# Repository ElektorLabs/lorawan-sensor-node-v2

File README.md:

# LoRa-Sensor-Node-v2

A comprehensive ESP32-S3 based sensor node that validates GPS positioning, LoRaWAN connectivity, SD card logging, battery charging, and deep-sleep power management without requiring the Arduino IDE.

## 🚀 Features

- **Multi-Peripheral Validation**: Powers and tests GPS, LoRa modem, SD logger, and battery charger
- **Smart Power Management**: Configurable deep-sleep cycles with peripheral power control
- **LoRaWAN Integration**: OTAA join with synthetic telemetry transmission
- **GPS Cold Start Handling**: Waits for valid GPS fix before LoRaWAN operations
- **Battery Management**: BQ25186 charger monitoring and configuration
- **Comprehensive Logging**: Tagged UART output and SD card data logging
- **Status Indicators**: LED patterns for system health monitoring

## 🔧 Hardware Components

### Core Platform
- **MCU**: ESP32-S3 Development Module
- **GPS Module**: Ebyte EWM108-GN05 (Allystar-compatible GNSS receiver)
- **LoRa Module**: Ebyte LoRaWAN module with AT command interface
- **Battery Charger**: BQ25186 Li-Ion battery management IC
- **Storage**: MicroSD card for data logging

### Pin Configuration

| Component | Pin | Function |
|-----------|-----|----------|
| **Power Control** |
| I2C Enable | GPIO 38 | I2C bus power control |
| LoRa Enable | GPIO 6 | LoRa module power |
| GPS Enable | GPIO 7 | GPS module power |
| **Status LEDs** |
| Red LED | GPIO 48 | Error/fault indication |
| Green LED | GPIO 47 | System status |
| **I2C Bus** |
| SDA | GPIO 10 | I2C data line |
| SCL | GPIO 9 | I2C clock line |
| **SD Card (SPI)** |
| MOSI | GPIO 11 | SPI data out |
| SCK | GPIO 12 | SPI clock |
| MISO | GPIO 13 | SPI data in |
| CS | GPIO 8 | Chip select |
| **LoRa UART** |
| RX | GPIO 4 | LoRa module RX |
| TX | GPIO 5 | LoRa module TX |
| **GPS UART** |
| RX | GPIO 21 | GPS module RX |
| TX | GPIO 14 | GPS module TX |

## ⚙️ Configuration

All configuration is centralized in `config.h` using `constexpr` constants:

### Timing Parameters
```cpp
constexpr unsigned long kGpsColdStartMs = 60000;        // GPS cold start window
constexpr unsigned long kGpsLockTimeoutMs = 180000;     // GPS fix timeout
constexpr unsigned long kSensorAcquisitionMs = 15000;   // Sensor reading time
constexpr uint64_t kDeepSleepIntervalUs = 60ULL * 1000000ULL; // Sleep interval
constexpr unsigned long kLoraJoinRetryMs = 15000;       // LoRa join retry
```

### Power Management
```cpp
constexpr bool kEnableDeepSleep = true;     // Enable ESP32 deep sleep
constexpr bool kEnableStatusLeds = true;    // Enable LED indicators
constexpr float kChargeTargetCurrentMa = 520.0f;   // Battery charge current (5-1000 mA)
constexpr float kInputCurrentLimitMa = 665.0f;     // Input current limit (50-665 mA)
```

### LoRaWAN Credentials
```cpp
constexpr LoraCredentials kLoraCredentials{
    "xxxxxxxxxxxxxxxx",                    // Device EUI
    "0000000000000000",                    // Application EUI
    "xxxxxxxxxxxxxxxxxxxxxxxxxxxxxx",   // Application Key
};
```

### GPS Power Configuration
```cpp
constexpr AllystarGpsPowerConfig kGpsPowerConfig{
    true,    // Enable GPS sleep/wake commands
    90000,   // Sleep duration (90 seconds)
    0x01,    // Sleep action (deep sleep)
    0x11,    // Wake mode (start command)
};
```

## 🔄 Operation Flow

1. **System Wake**: ESP32 wakes from deep sleep, powers peripheral rails
2. **GPS Cold Start**: Waits for GPS module to acquire satellite fix
3. **LoRaWAN Join**: Performs OTAA join once GPS is ready (or timeout expires)
4. **Data Collection**: Gathers GPS coordinates and battery telemetry
5. **Transmission**: Sends telemetry via LoRaWAN uplink
6. **Logging**: Records data to SD card with timestamps
7. **Sleep Preparation**: Powers down GPS with Allystar sleep commands
8. **Deep Sleep**: ESP32 enters deep sleep for configured interval

## 📊 Serial Output

The firmware provides tagged serial output at 115200 baud:

```
[Pwr ] Wake reason: Timer
[GPS ] Powering GPS module...
[LoRa] Powering LoRa module...
[GPS ] NMEA: $GNGGA,123456.00,4012.34567,N,07412.34567,W,1,08,1.2,45.6,M,33.2,M,,*5A
[LoRa] AT+JOIN
[LoRa] Event: join confirmed
[LoRa] Sending telemetry: 4012.34567,-07412.34567,45.6,4.12,85
[Chg ] Battery: 4.12V, Charge: 85%, Temp: 25°C
[Pwr ] Entering deep sleep for 60 seconds
```

## 📁 File Structure

```
LoRa-SenseNode-v2/
├── LoRa-SenseNode-v2.ino    # Main firmware file
├── config.h                 # Configuration constants
├── Bq25186.h               # Battery charger interface
├── EbyteGpsParser.h        # GPS NMEA parser
├── LoraAtHelpers.h         # LoRaWAN AT command helpers
├── SdCardLogger.h          # SD card logging utilities
├── TaggedStream.h          # Serial output tagging
├── ProcessFlow.md          # Detailed process documentation
├── FirmwareOverview.md     # Architecture overview
└── docs/                   # Additional documentation
```

## 🔍 Troubleshooting

### LED Status Indicators
- **2 Red Blinks**: GPS fault or timeout
- **3 Red Blinks**: LoRa communication fault
- **Green Solid**: System operating normally
- **LEDs Off**: Status LEDs disabled in config

### Common Issues
1. **GPS Not Acquiring Fix**: Ensure clear sky view, check antenna connection
2. **LoRa Join Fails**: Verify credentials and gateway availability
3. **SD Card Errors**: Check card formatting (FAT32) and connections
4. **Power Issues**: Verify battery connection and charger configuration

### Debug Mode
Set `kEnableDebugSerial = true` and `kShowRawGps = true` in config.h for verbose output.

## 🛠️ Development

### Adding New Features
- Hardware tests: Create new sketches in `src/tests/<SketchName>/`
- Experiments: Use `src/claude-test/` for exploratory code
- Helper functions: Add to existing headers or create new ones as needed

### Testing Without Deep Sleep
Set `kEnableDeepSleep = false` in config.h to run continuous loops for bench testing.

## 📄 License

This project is licensed under the GNU License - see the [LICENSE](LICENSE) file for details.

## 🤝 Contributing

1. Fork the repository
2. Create a feature branch (`git checkout -b feature/amazing-feature`)
3. Commit your changes (`git commit -m 'Add amazing feature'`)
4. Push to the branch (`git push origin feature/amazing-feature`)
5. Open a Pull Request

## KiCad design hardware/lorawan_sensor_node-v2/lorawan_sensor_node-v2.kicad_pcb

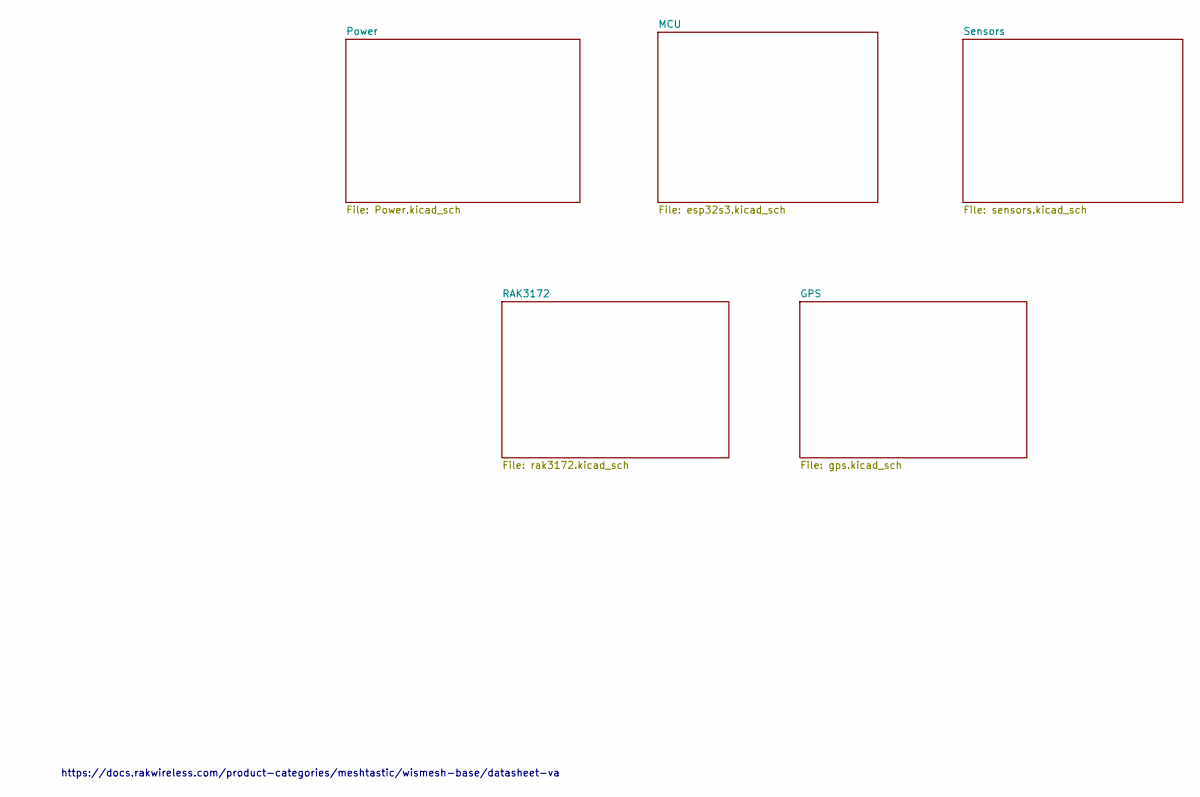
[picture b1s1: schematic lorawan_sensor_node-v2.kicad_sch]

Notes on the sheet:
https://docs.rakwireless.com/product-categories/meshtastic/wismesh-base/datasheet-va

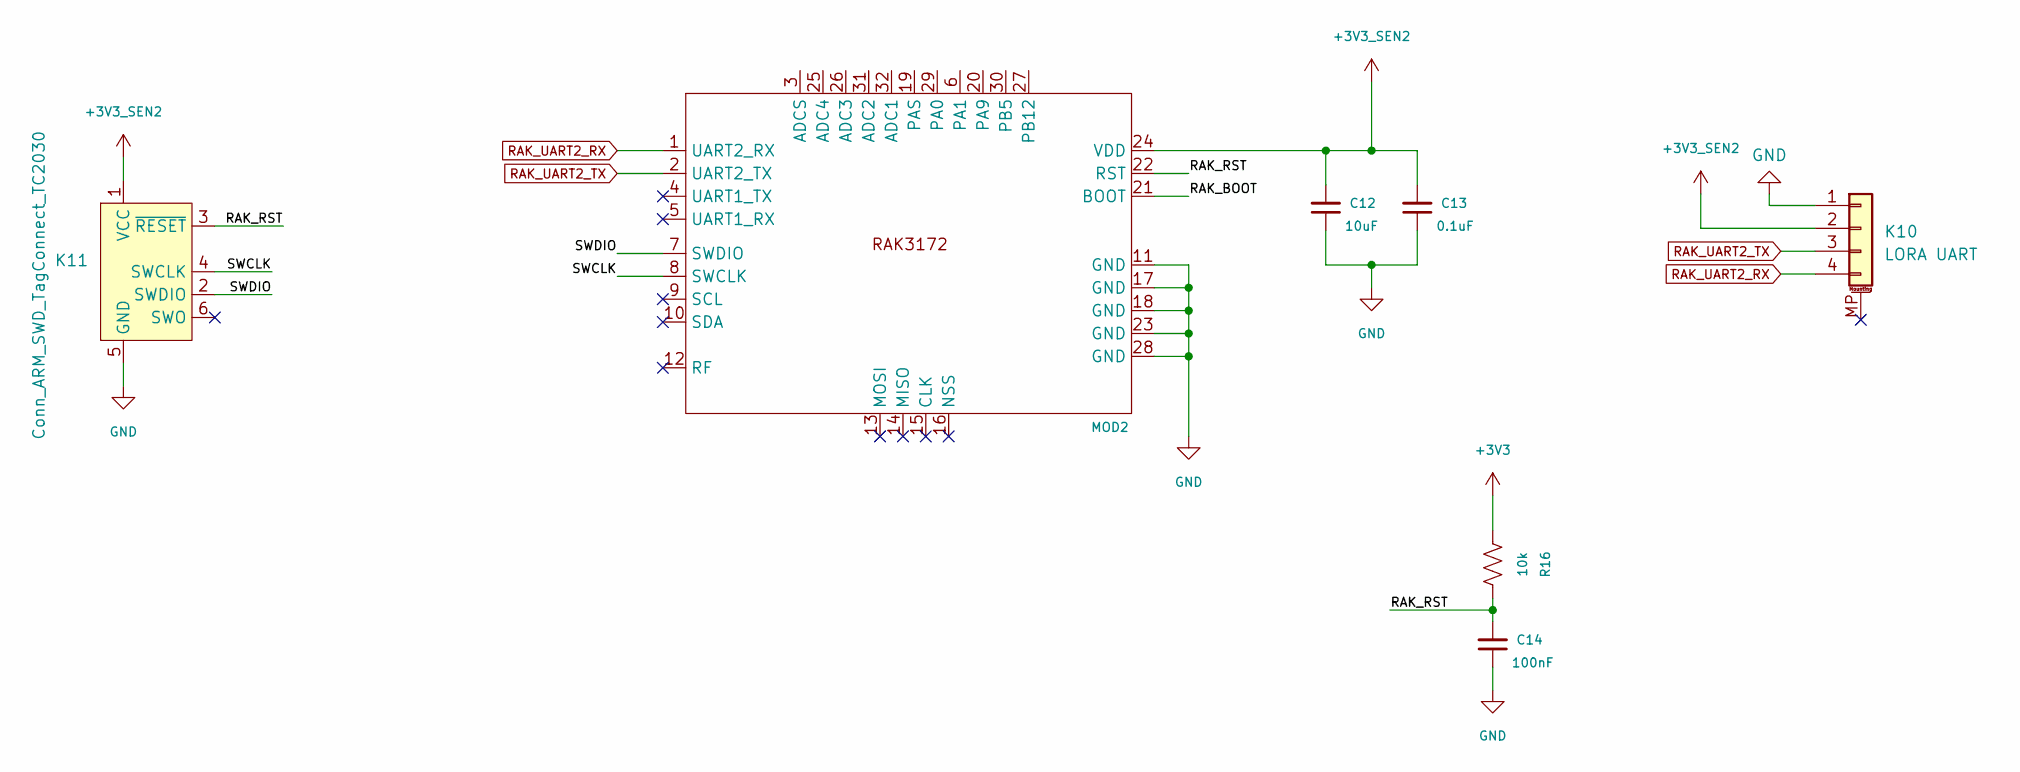
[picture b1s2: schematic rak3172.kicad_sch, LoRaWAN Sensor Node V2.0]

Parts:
C12: 10uF; C_0402_1005Metric_Pad0.74x0.62mm_HandSolder; Mouser Part Number 81-GRM155R60J475ME7D
C13: 0.1uF; C_0402_1005Metric_Pad0.74x0.62mm_HandSolder; Mouser Part Number 81-GRM155R60J475ME7D
C14: 100nF; C_0402_1005Metric_Pad0.74x0.62mm_HandSolder; Mouser Part Number 81-GRM155R60J475ME7D
K10: LORA UART; JST_PH_S4B-PH-SM4-TB_1x04-1MP_P2.00mm_Horizontal; Manufacturer_Part_Number Connector_JST:JST_PH_S4B-PH-SM4-TB_1x04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
K11: Conn_ARM_SWD_TagConnect_TC2030; Tag-Connect_TC2030-IDC-NL_2x03_P1.27mm_Vertical
MOD2: RAK3172; Manufacturer_Part_Number RAK3172
R16: 10k; R_0603_1608Metric; Manufacturer_Part_Number RCS060310K0FKEA; Mouser Part Number 71-RCS060310K0FKEA

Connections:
+3V3: R16.2; also elsewhere on the board
+3V3_SEN2: C12.2, C13.2, K10.2, K11.1 (VCC), MOD2.24 (VDD); also elsewhere on the board
/RAK3172/RAK_BOOT: MOD2.21 (BOOT)
/RAK3172/RAK_RST: C14.2, K11.3 (~RESET), MOD2.22 (RST), R16.1
/RAK3172/SWCLK: K11.4 (SWCLK), MOD2.8 (SWCLK)
/RAK3172/SWDIO: K11.2 (SWDIO), MOD2.7 (SWDIO)
GND: C12.1, C13.1, C14.1, K10.1, K11.5 (GND), MOD2.11 (GND), MOD2.17 (GND), MOD2.18 (GND), MOD2.23 (GND), MOD2.28 (GND); also elsewhere on the board
RAK_UART2_RX: K10.4, MOD2.1 (UART2_RX); also elsewhere on the board
RAK_UART2_TX: K10.3, MOD2.2 (UART2_TX); also elsewhere on the board

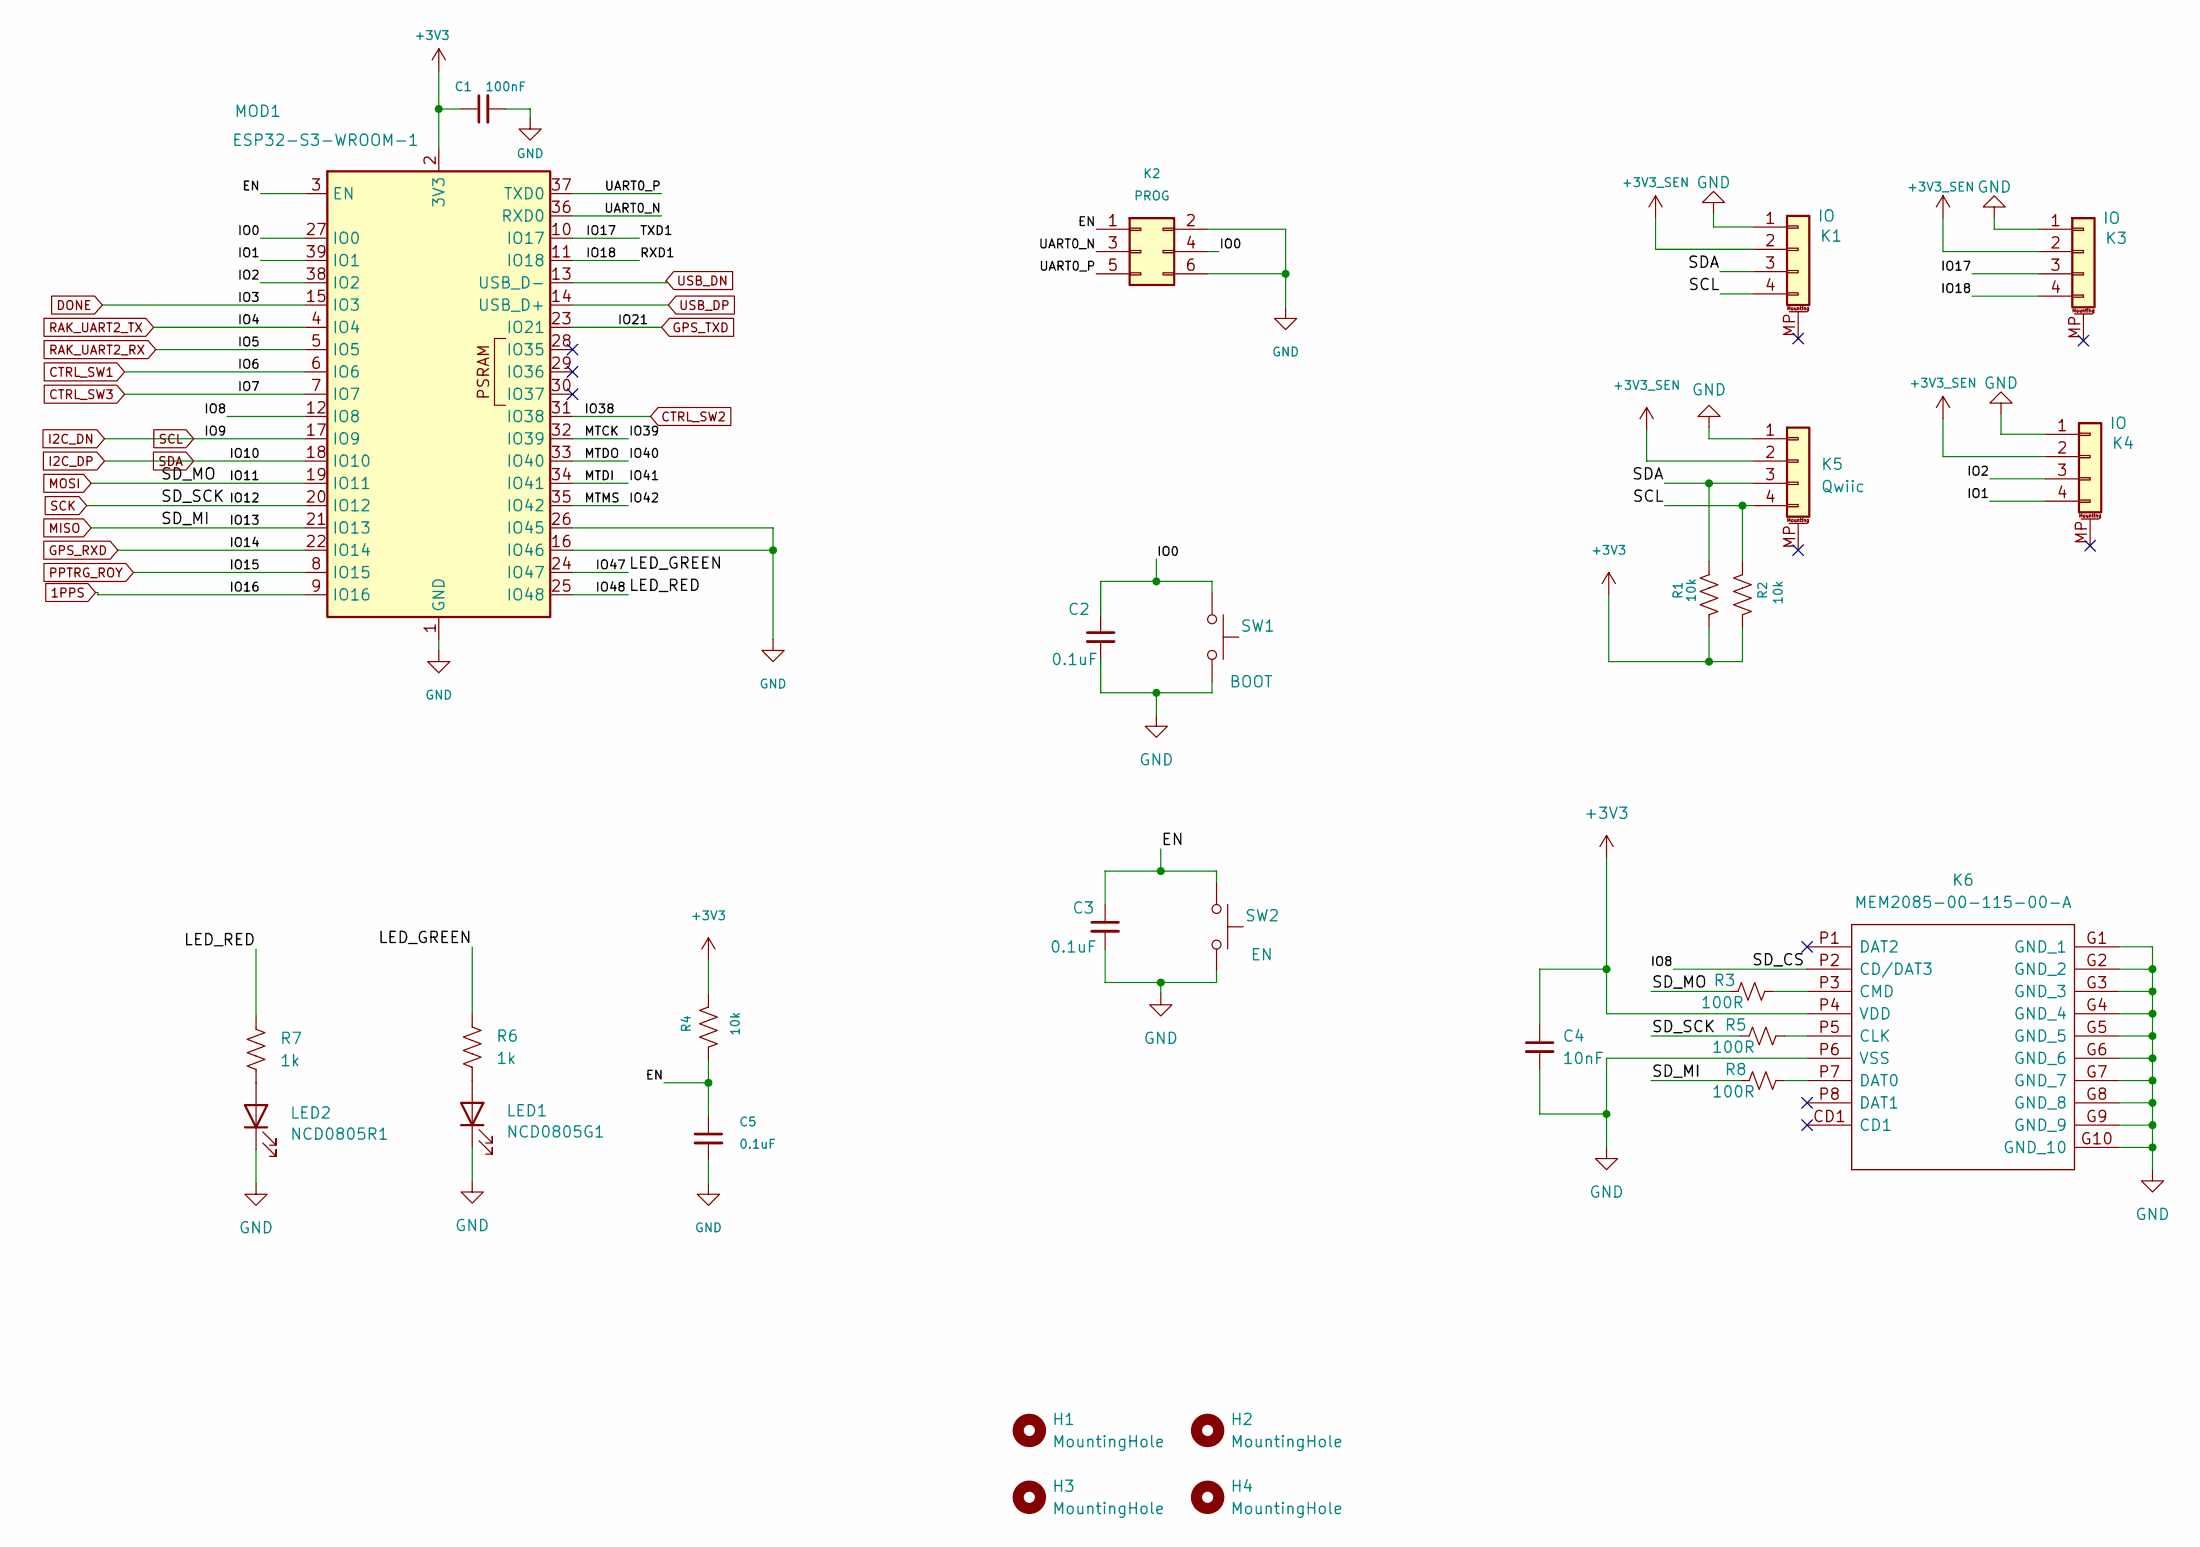
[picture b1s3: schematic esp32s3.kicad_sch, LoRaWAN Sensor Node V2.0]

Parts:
C1: 100nF; C_0603_1608Metric; Manufacturer_Part_Number C1608X7R1H104K080AA; Mouser Part Number 810-C1608X7R1H104K
C2, C3: 0.1uF; C_0805_2012Metric_Pad1.18x1.45mm_HandSolder; Manufacturer_Part_Number C0805C104M5RACTU; Mouser Part Number 80-C0805C104M5R
C4: 10nF; C_0402_1005Metric_Pad0.74x0.62mm_HandSolder; Manufacturer_Part_Number C0402C103K5RAC7411; Mouser Part Number 80-C0402C103K5R7411
C5: 0.1uF; C_0603_1608Metric; Manufacturer_Part_Number C1608X7R1H104K080AA; Mouser Part Number 810-C1608X7R1H104K
H1, H2, H3, H4: MountingHole; MountingHole_3.2mm_M3
K1, K3, K4: IO; JST_PH_S4B-PH-SM4-TB_1x04-1MP_P2.00mm_Horizontal; Manufacturer_Part_Number JST_PH_S4B-PH-SM4-TB_1x04-1MP_P2.00mm_H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
K2: PROG; PinHeader_2x03_P2.54mm_Vertical; Manufacturer_Part_Number PinHeader_2x03_P2.54mm_Vertical
K5: Qwiic; JST_SH_SM04B-SRSS-TB_1x04-1MP_P1.00mm_Horizontal; Manufacturer_Part_Number JST_SH_SM04B-SRSS-TB_1x04-1MP_P1.00mm_H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
K6: MEM2085-00-115-00-A; MEM20850011500A; Mouser Part Number 640-MEM20850011500A
LED1: NCD0805G1; LED_0805_2012Metric_Pad1.15x1.40mm_HandSolder; Manufacturer_Part_Number NCD0805G1
LED2: NCD0805R1; LED_0805_2012Metric_Pad1.15x1.40mm_HandSolder; Manufacturer_Part_Number NCD0805R1
MOD1: ESP32-S3-WROOM-1; Manufacturer_Part_Number ESP32-S3-WROOM-1
R1, R2, R4: 10k; R_0603_1608Metric; Manufacturer_Part_Number RCS060310K0FKEA; Mouser Part Number 71-RCS060310K0JNEA
R3, R5, R8: 100R; R_0603_1608Metric; Manufacturer_Part_Number MCT0603PD1000DP500; Mouser Part Number 594-MCT0603PD1000DP5
R6, R7: 1k; R_0805_2012Metric_Pad1.20x1.40mm_HandSolder; Manufacturer_Part_Number CHP0805-FX-1001ELF; Mouser Part Number 652-CHP0805FX1001ELF
SW1: BOOT; SKRKAEE020; Manufacturer_Part_Number SKRKAEE020; Mouser Part Number SKRKAEE020
SW2: EN; SKRKAEE020; Manufacturer_Part_Number SKRKAEE020; Mouser Part Number SKRKAEE020

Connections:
1PPS: MOD1.9 (IO16); also elsewhere on the board
+3V3: C1.1, C4.1, K6.P4 (VDD), MOD1.2 (3V3), R1.1, R2.1, R4.2; also elsewhere on the board
+3V3_SEN: K1.2, K3.2, K4.2, K5.2; also elsewhere on the board
/MCU/EN: C3.1, C5.1, K2.1, MOD1.3 (EN), R4.1, SW2.1
/MCU/IO0: C2.1, K2.4, MOD1.27 (IO0), SW1.1
/MCU/IO1: K4.4, MOD1.39 (IO1)
/MCU/IO2: K4.3, MOD1.38 (IO2)
/MCU/IO8: K6.P2 (CD/DAT3), MOD1.12 (IO8)
/MCU/IO17: K3.3, MOD1.10 (IO17)
/MCU/IO18: K3.4, MOD1.11 (IO18)
/MCU/IO39: MOD1.32 (IO39)
/MCU/IO40: MOD1.33 (IO40)
/MCU/IO41: MOD1.34 (IO41)
/MCU/IO42: MOD1.35 (IO42)
/MCU/IO47: MOD1.24 (IO47), R6.2
/MCU/IO48: MOD1.25 (IO48), R7.2
/MCU/UART0_N: K2.3, MOD1.36 (RXD0)
/MCU/UART0_P: K2.5, MOD1.37 (TXD0)
CTRL_SW1: MOD1.6 (IO6); also elsewhere on the board
CTRL_SW2: MOD1.31 (IO38); also elsewhere on the board
CTRL_SW3: MOD1.7 (IO7); also elsewhere on the board
DONE: MOD1.15 (IO3); also elsewhere on the board
GND: C1.2, C2.2, C3.2, C4.2, C5.2, K1.1, K2.2, K2.6, K3.1, K4.1, K5.1, K6.G1 (GND_1), K6.G2 (GND_2), K6.G3 (GND_3), K6.G4 (GND_4), K6.G5 (GND_5), K6.G6 (GND_6), K6.G7 (GND_7), K6.G8 (GND_8), K6.G9 (GND_9), K6.G10 (GND_10), K6.P6 (VSS), LED1.1 (K), LED2.1 (K), MOD1.1 (GND), MOD1.16 (IO46), MOD1.26 (IO45), MOD1.40 (GND), MOD1.41 (GND), SW1.2, SW2.2; also elsewhere on the board
GPS_RXD: MOD1.22 (IO14); also elsewhere on the board
GPS_TXD: MOD1.23 (IO21); also elsewhere on the board
I2C_DN: K1.4, K5.4, MOD1.17 (IO9), R2.2; also elsewhere on the board
I2C_DP: K1.3, K5.3, MOD1.18 (IO10), R1.2; also elsewhere on the board
MISO: MOD1.21 (IO13), R8.1
MOSI: MOD1.19 (IO11), R3.1
unnamed: K6.P5 (CLK), R5.2
unnamed: K6.P3 (CMD), R3.2
unnamed: K6.P7 (DAT0), R8.2
unnamed: LED1.2 (A), R6.1
unnamed: LED2.2 (A), R7.1
PPTRG_ROY: MOD1.8 (IO15); also elsewhere on the board
RAK_UART2_RX: MOD1.5 (IO5); also elsewhere on the board
RAK_UART2_TX: MOD1.4 (IO4); also elsewhere on the board
SCK: MOD1.20 (IO12), R5.1
USB_DN: MOD1.13 (USB_D-); also elsewhere on the board
USB_DP: MOD1.14 (USB_D+); also elsewhere on the board

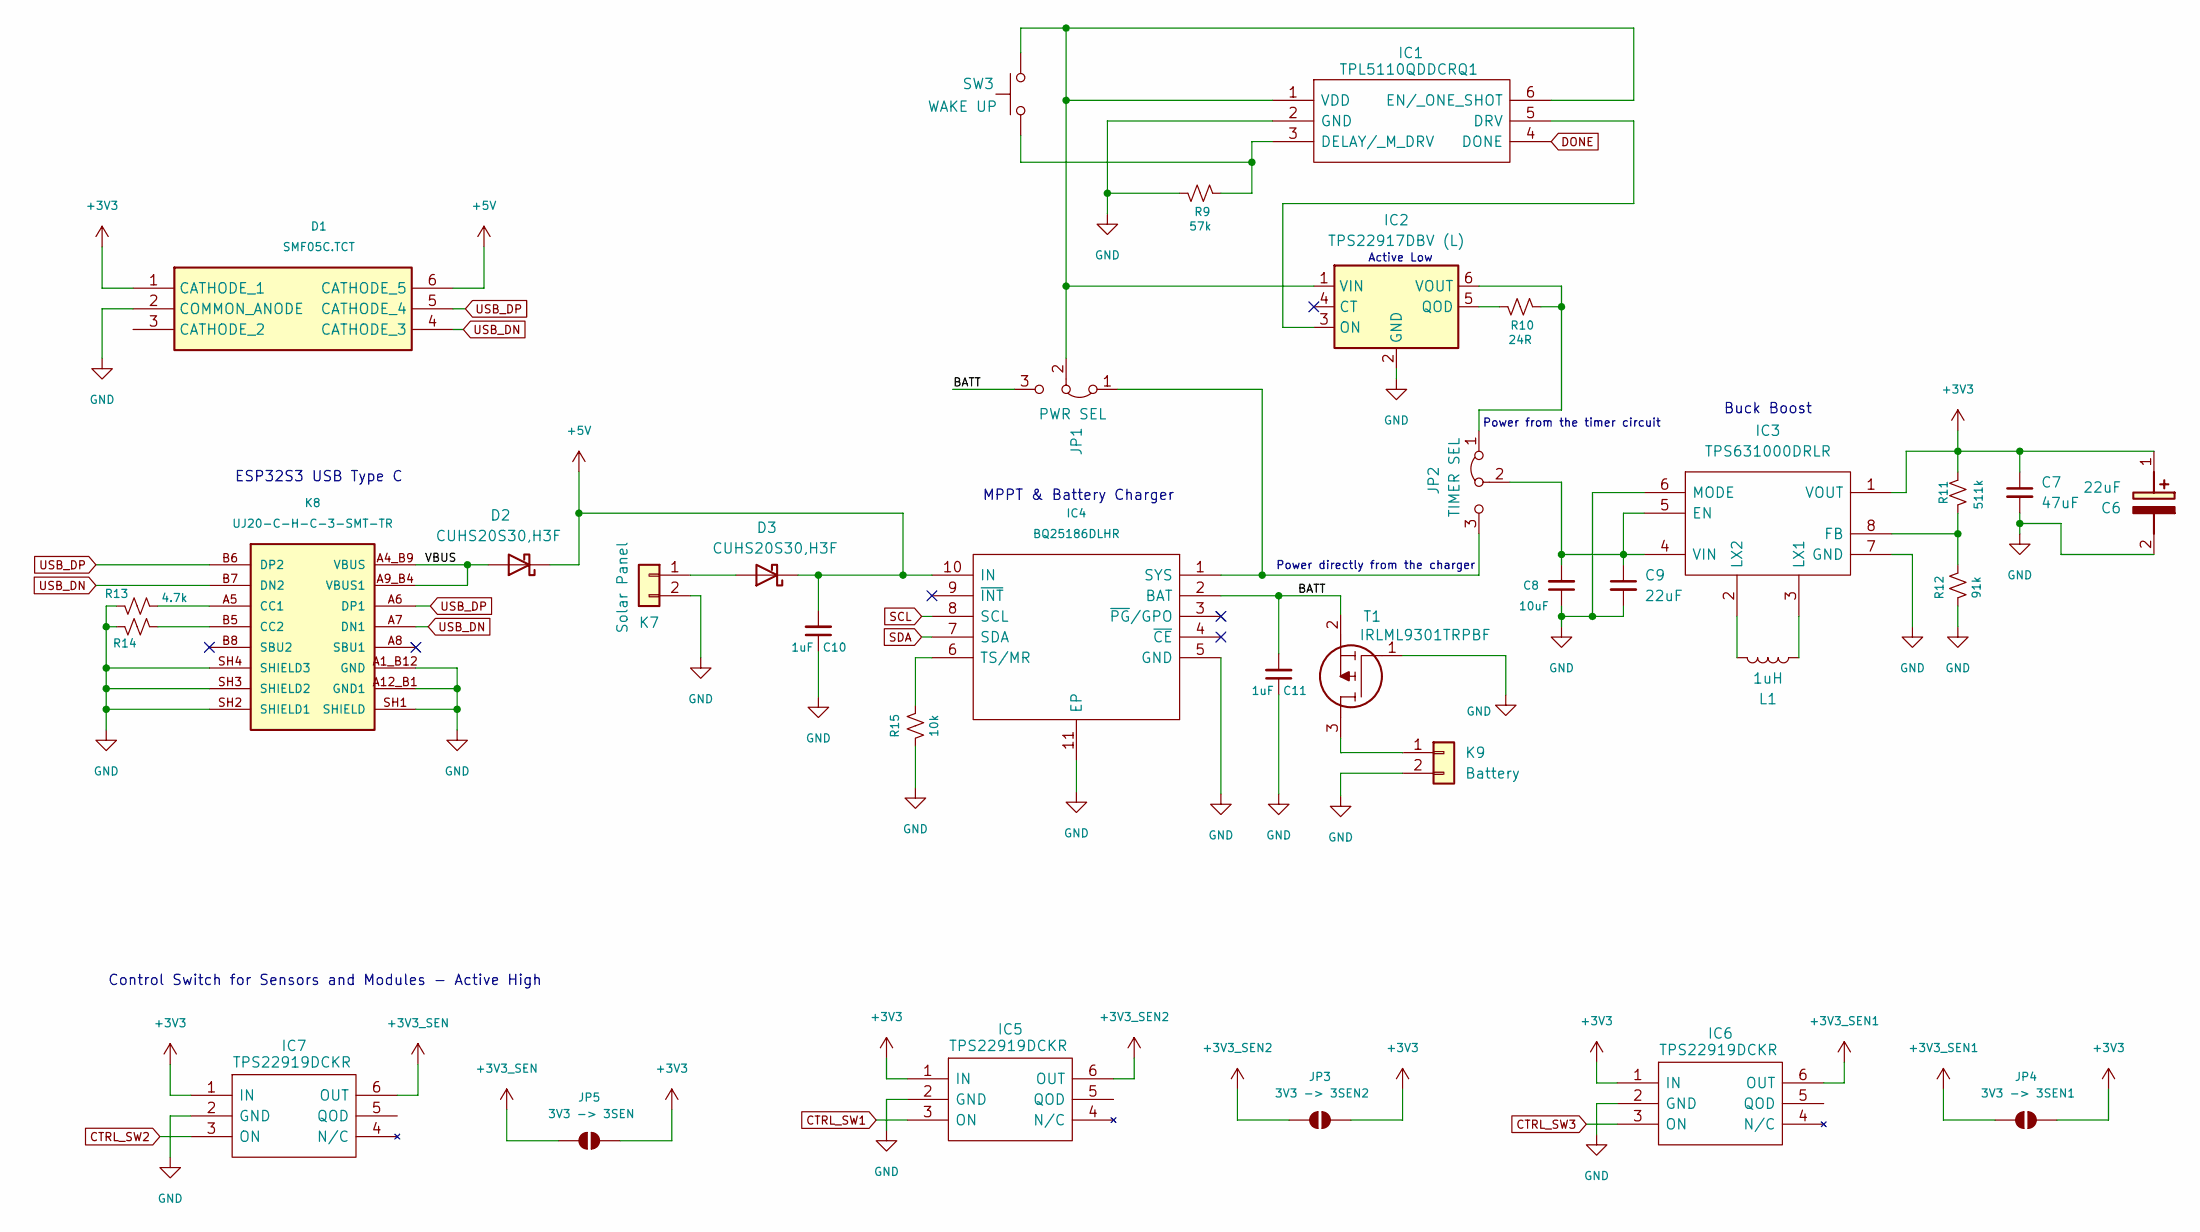
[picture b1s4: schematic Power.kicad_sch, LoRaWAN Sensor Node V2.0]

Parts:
C6: 22uF; CAPAE530X550N; Mouser Part Number 710-865080442004
C7: 47uF; C_0805_2012Metric; Manufacturer_Part_Number GRM219R60J476ME44
C8: 10uF; C_0402_1005Metric_Pad0.74x0.62mm_HandSolder; Mouser Part Number 81-GRM155R60J475ME7D
C9: 22uF; C_0603_1608Metric; Manufacturer_Part_Number GRM187R61A226ME15
C10, C11: 1uF; C_0402_1005Metric_Pad0.74x0.62mm_HandSolder; Mouser Part Number 81-GRM155R60J475ME7D
D1: SMF05C.TCT; SOT65P210X110-6N; Mouser Part Number 947-SMF05C.TCT
D2, D3: CUHS20S30,H3F; CUHS20S40H3F; Mouser Part Number 757-CUHS20S30H3F
IC1: TPL5110QDDCRQ1; SOT95P280X110-6N; Mouser Part Number 595-TPL5110QDDCRQ1
IC2: TPS22917DBV (L); SOT-23-6; Manufacturer_Part_Number TPS22917DBV
IC3: TPS631000DRLR; SOTFL50P160X60-8N; Mouser Part Number 595-TPS631000DRLR
IC4: BQ25186DLHR; SON40P220X200X80-11N; Mouser Part Number 595-BQ25186DLHR
IC5, IC6, IC7: TPS22919DCKR; SOT65P210X110-6N; Mouser Part Number 595-TPS22919DCKR
JP1: PWR SEL; PinHeader_1x03_P2.54mm_Vertical
JP2: TIMER SEL; PinHeader_1x03_P2.54mm_Vertical
JP3: 3V3 -> 3SEN2; SolderJumper-2_P1.3mm_Open_RoundedPad1.0x1.5mm
JP4: 3V3 -> 3SEN1; SolderJumper-2_P1.3mm_Open_RoundedPad1.0x1.5mm
JP5: 3V3 -> 3SEN; SolderJumper-2_P1.3mm_Open_RoundedPad1.0x1.5mm
K7: Solar Panel; JST_PH_S2B-PH-K_1x02_P2.00mm_Horizontal; Manufacturer_Part_Number JST_PH_S2B-PH-K_1x02_P2.00mm_Horizontal
K8: UJ20-C-H-C-3-SMT-TR; CUI_UJ20-C-H-C-3-SMT-TR; PARTREV 1.0
K9: Battery; JST_PH_S2B-PH-K_1x02_P2.00mm_Horizontal; Manufacturer_Part_Number JST_PH_S2B-PH-K_1x02_P2.00mm_Horizontal
L1: 1uH; 1285ASH1R0MP2; Mouser Part Number 81-DFE201610P-1R0MP2
R9: 57k; R_0402_1005Metric; Manufacturer_Part_Number RK73H1ETTP5762F; Mouser Part Number 660-RK73H1ETTP5762F
R10: 24R; R_0402_1005Metric; Manufacturer_Part_Number CRCW040224R0FKED; Mouser Part Number 71-CRCW040224R0FKED
R11: 511k; R_0402_1005Metric; Manufacturer_Part_Number ERJ-2RKF5113X; Mouser Part Number 667-ERJ-2RKF5113X
R12: 91k; R_0402_1005Metric; Manufacturer_Part_Number ERJ-2RKF9102X; Mouser Part Number 667-ERJ-2RKF9102X
R13, R14: 4.7k; R_0603_1608Metric; Manufacturer_Part_Number RCS06034K70FKEA; Mouser Part Number 71-RCS06034K70FKEA
R15: 10k; R_0402_1005Metric; Manufacturer_Part_Number RCS06034K70FKEA; Mouser Part Number 71-RCS06034K70FKEA
SW3: WAKE UP; SKRKAEE020; Manufacturer_Part_Number SKRKAEE020; Mouser Part Number SKRKAEE020
T1: IRLML9301TRPBF; SOT95P237X112-3N; Mouser Part Number 942-IRLML9301TRPBF

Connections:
+3V3: C6.1 (+), C7.1, D1.1 (CATHODE_1), IC3.1 (VOUT), IC5.1 (IN), IC6.1 (IN), IC7.1 (IN), JP3.2 (B), JP4.2 (B), JP5.2 (B), R11.2; also elsewhere on the board
+3V3_SEN: IC7.6 (OUT), JP5.1 (A); also elsewhere on the board
+3V3_SEN1: IC6.6 (OUT), JP4.1 (A); also elsewhere on the board
+3V3_SEN2: IC5.6 (OUT), JP3.1 (A); also elsewhere on the board
+5V: C10.2, D1.6 (CATHODE_5), D2.1 (K), D3.1 (K), IC4.10 (IN); also elsewhere on the board
/Power/BATT: C11.2, IC4.2 (BAT), JP1.3 (B), T1.2
/Power/VBUS: D2.2 (A), K8.A4_B9 (VBUS), K8.A9_B4 (VBUS1)
CTRL_SW1: IC5.3 (ON); also elsewhere on the board
CTRL_SW2: IC7.3 (ON); also elsewhere on the board
CTRL_SW3: IC6.3 (ON); also elsewhere on the board
DONE: IC1.4 (DONE); also elsewhere on the board
GND: C6.2 (-), C7.2, C8.1, C9.2, C10.1, C11.1, D1.2 (COMMON_ANODE), IC1.2 (GND), IC2.2 (GND), IC3.6 (MODE), IC3.7 (GND), IC4.5 (GND), IC4.11 (EP), IC5.2 (GND), IC6.2 (GND), IC7.2 (GND), K7.2, K8.A1_B12 (GND), K8.A12_B1 (GND1), K8.SH1 (SHIELD), K8.SH2 (SHIELD1), K8.SH3 (SHIELD2), K8.SH4 (SHIELD3), K9.2, R9.2, R12.1, R13.1, R14.1, R15.1, T1.1; also elsewhere on the board
I2C_DN: IC4.8 (SCL); also elsewhere on the board
I2C_DP: IC4.7 (SDA); also elsewhere on the board
unnamed: D3.2 (A), K7.1
unnamed: IC1.3 (DELAY/_M_DRV), R9.1, SW3.2
unnamed: IC1.5 (DRV), IC2.3 (ON)
unnamed: IC1.1 (VDD), IC1.6 (EN/_ONE_SHOT), IC2.1 (VIN), JP1.2 (C), SW3.1
unnamed: IC2.5 (QOD), R10.2
unnamed: IC2.6 (VOUT), JP2.1 (A), R10.1
unnamed: C8.2, C9.1, IC3.4 (VIN), IC3.5 (EN), JP2.2 (C)
unnamed: IC3.8 (FB), R11.1, R12.2
unnamed: IC3.3 (LX1), L1.2
unnamed: IC3.2 (LX2), L1.1
unnamed: IC4.1 (SYS), JP1.1 (A), JP2.3 (B)
unnamed: IC4.6 (TS/MR), R15.2
unnamed: K8.A5 (CC1), R13.2
unnamed: K8.B5 (CC2), R14.2
unnamed: K9.1, T1.3
USB_DN: D1.4 (CATHODE_3), K8.A7 (DN1), K8.B7 (DN2); also elsewhere on the board
USB_DP: D1.5 (CATHODE_4), K8.A6 (DP1), K8.B6 (DP2); also elsewhere on the board

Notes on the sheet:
Buck Boost
Power directly from the charger
ESP32S3 USB Type C
MPPT & Battery Charger
Power from the timer circuit
Active Low
Control Switch for Sensors and Modules - Active High

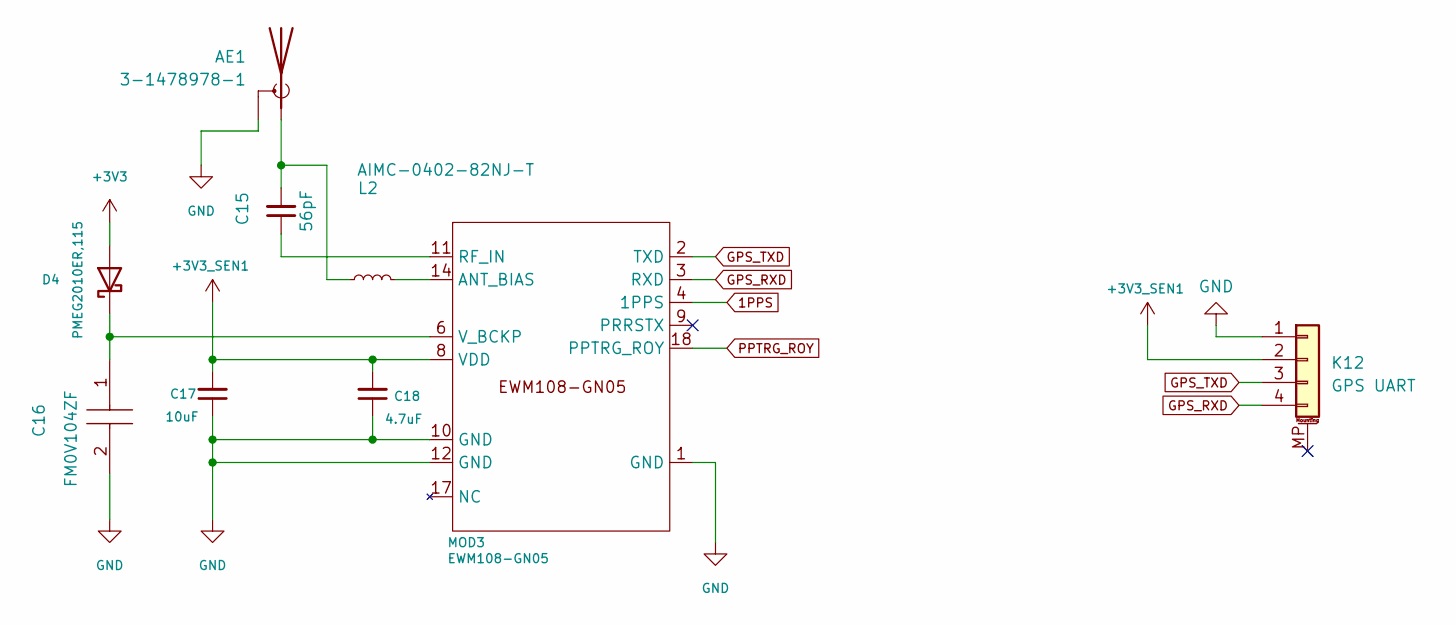
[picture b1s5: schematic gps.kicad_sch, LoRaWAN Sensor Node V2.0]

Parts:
AE1: 3-1478978-1; 314789781; Mouser Part Number 571-3-1478978-1
C15: 56pF; C_0603_1608Metric_Pad1.08x0.95mm_HandSolder; Manufacturer_Part_Number 600S560KT250T; Mouser Part Number 581-600S560KT250T
C16: FM0V104ZF; Mouser Part Number 80-FM0V104ZF
C17: 10uF; C_0402_1005Metric_Pad0.74x0.62mm_HandSolder; Mouser Part Number 81-GRM155R60J475ME7D
C18: 4.7uF; C_0402_1005Metric_Pad0.74x0.62mm_HandSolder; Mouser Part Number 81-GRM155R60J475ME7D
D4: PMEG2010ER,115; PMEG2010ER115; Mouser Part Number 771-PMEG2010ER115
K12: GPS UART; JST_PH_S4B-PH-SM4-TB_1x04-1MP_P2.00mm_Horizontal; Manufacturer_Part_Number Connector_JST:JST_PH_S4B-PH-SM4-TB_1x04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
L2: AIMC-0402-82NJ-T; INDC1005X65N; Manufacturer_Part_Number AIMC-0402-82NJ-T
MOD3: EWM108-GN05; PCBComponent_1; Manufacturer_Part_Number EWM108-GN05

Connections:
1PPS: MOD3.4 (1PPS); also elsewhere on the board
+3V3: D4.2 (A); also elsewhere on the board
+3V3_SEN1: C17.2, C18.2, K12.2, MOD3.8 (VDD); also elsewhere on the board
GND: AE1.1 (eShield), AE1.2 (Shield), AE1.3 (Shield), AE1.4 (Shield), C16.2, C17.1, C18.1, K12.1, MOD3.1 (GND), MOD3.10 (GND), MOD3.12 (GND); also elsewhere on the board
GPS_RXD: K12.4, MOD3.3 (RXD); also elsewhere on the board
GPS_TXD: K12.3, MOD3.2 (TXD); also elsewhere on the board
unnamed: AE1.5 (A), C15.2, L2.1
unnamed: C16.1, D4.1 (K), MOD3.6 (V_BCKP)
unnamed: L2.2, MOD3.14 (ANT_BIAS)
unnamed: C15.1, MOD3.11 (RF_IN)
PPTRG_ROY: MOD3.18 (PPTRG_ROY); also elsewhere on the board

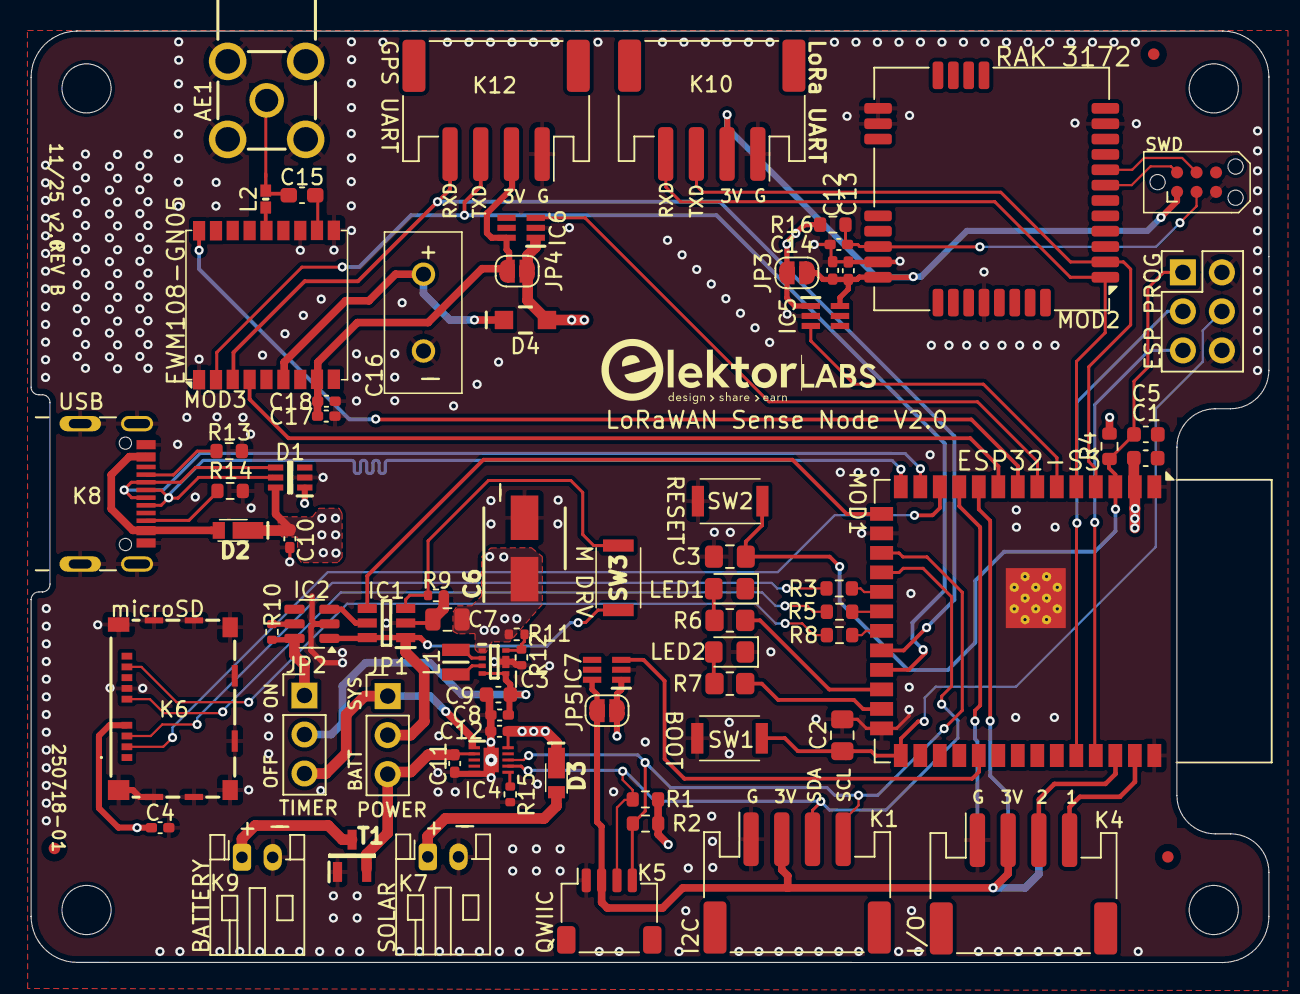
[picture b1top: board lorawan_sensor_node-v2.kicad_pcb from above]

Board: 4 copper layers, 80.6 x 60.6 mm, 79 parts (1 on the bottom side), 63 nets.

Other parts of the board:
C12#2: 4.7uF; C_0402_1005Metric_Pad0.74x0.62mm_HandSolder

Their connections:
+5V: C12#2.2; also elsewhere on the board
GND: C12#2.1; also elsewhere on the board

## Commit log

2026-01-28 Add LoRaWAN Sensor Node v2 hardware and firmware
    Initial commit of hardware design files for the LoRaWAN Sensor Node v2, including KiCad schematics, PCB layout, BOMs (old and new), and supporting documentation. Also adds initial firmware source fil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
2026-01-28 Revise README for LoRa-Sensor-Node-v2
    Updated project name and expanded README with detailed features, hardware components, configuration, operation flow, troubleshooting, development guidelines, and contributing instructions.

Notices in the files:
README.md:
License: MIT
